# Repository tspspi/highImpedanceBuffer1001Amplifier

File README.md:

# Simple combined buffer and 1001x amplifier

This is a simple circuit that combines two OpAmps with 1 GHz
bandwidth to form a buffer amplifier followed by an 1001 times
amplifying amplifier.

This circuit has been designed to measure the beam profile of
an low current electron beam. The shunt has been designed as wire
resistor to be easily adaptable. The OpAmps have been selected
with up to 1 GHz bandwidth to allow for measurement of deflection
frequency inside an modulated beam.

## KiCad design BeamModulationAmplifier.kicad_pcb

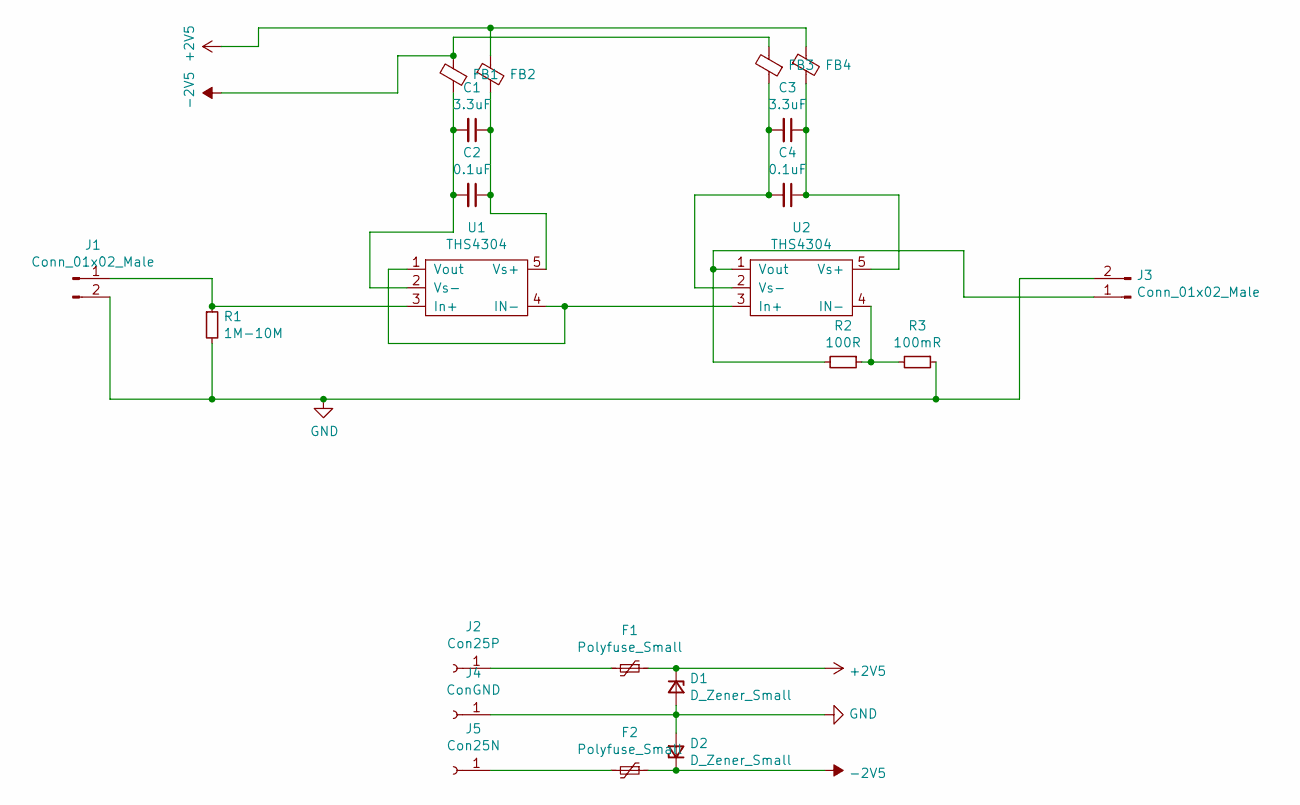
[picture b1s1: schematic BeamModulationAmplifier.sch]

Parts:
C1, C3: 3.3uF; R_0805_2012Metric
C2, C4: 0.1uF; R_0805_2012Metric
D1, D2: D_Zener_Small; Mini2
F1, F2: Polyfuse_Small; Generic2016
FB1, FB2, FB3, FB4: Ferrite_Bead_Small; R_0603_1608Metric; FarnellNo 3282195
J1, J3: Conn_01x02_Male; BNC_Amphenol_B6252HB-NPP3G-50_Horizontal; FarnellNo 1076296
J2: Con25P; 24.243
J4: ConGND; 24.243
J5: Con25N; 24.243
R1: 1M-10M; R_Axial_DIN0309_L9.0mm_D3.2mm_P15.24mm_Horizontal
R2: 100R; R_0805_2012Metric
R3: 100mR; R_0805_2012Metric
U1, U2: THS4304; SOT-23-5

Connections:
+2V5: D1.1 (K), F1.1, FB2.1, FB4.1
-2V5: D2.1 (K), F2.1, FB1.2, FB3.2
GND: D1.2 (A), D2.2 (A), J1.2, J3.2, J4.1, R1.2, R3.1
unnamed: C1.1, C2.1, FB2.2, U1.5 (Vs+)
unnamed: C1.2, C2.2, FB1.1, U1.2 (Vs-)
unnamed: C3.1, C4.1, FB4.2, U2.5 (Vs+)
unnamed: C3.2, C4.2, FB3.1, U2.2 (Vs-)
unnamed: F1.2, J2.1, J2.2
unnamed: F2.2, J5.1, J5.2
unnamed: J1.1, R1.1, U1.3 (In+)
unnamed: J3.1, R2.2, U2.1 (Vout)
unnamed: R2.1, R3.2, U2.4 (IN-)
unnamed: U1.1 (Vout), U1.4 (IN-), U2.3 (In+)

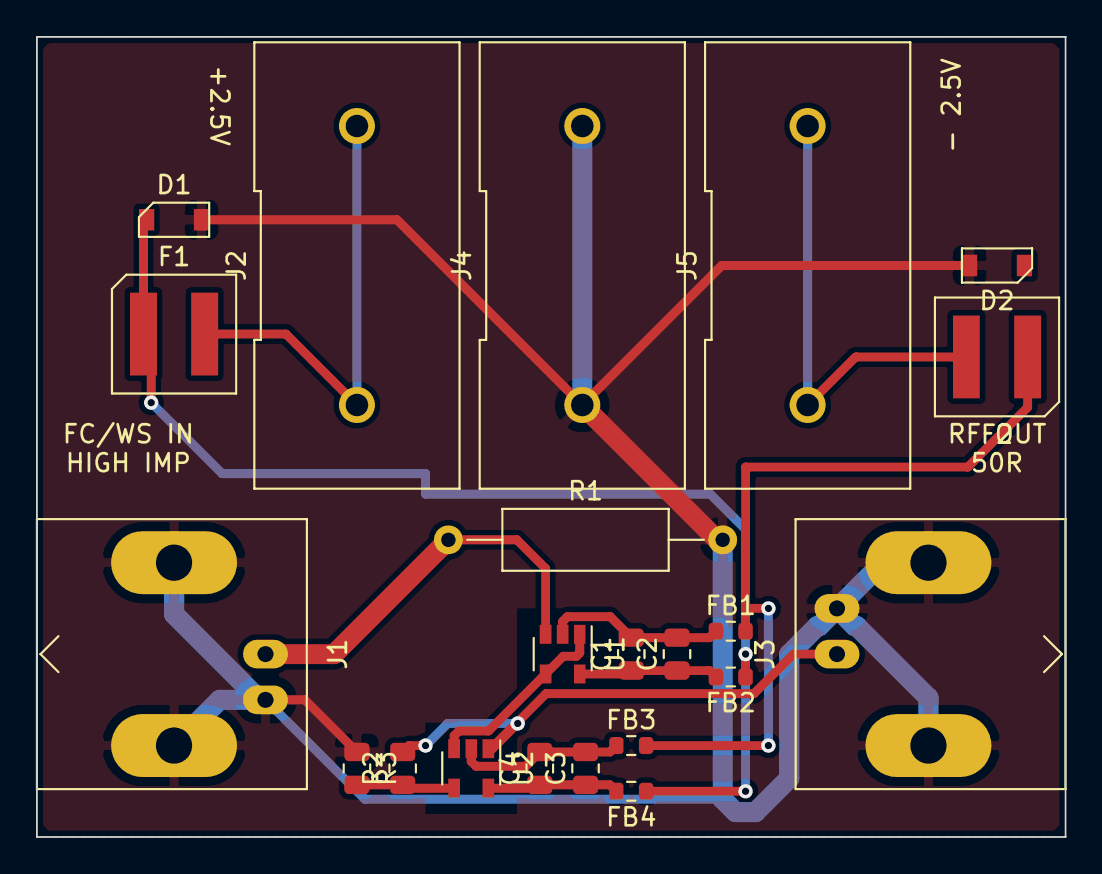
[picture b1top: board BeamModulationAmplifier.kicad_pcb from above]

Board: 2 copper layers, 57.2 x 44.5 mm, 22 parts (0 on the bottom side), 13 nets.

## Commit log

2020-10-29 Initial commit including Farnell BOM
2020-10-29 Added license
2020-10-29 Added images
2020-10-29 Adding images to README
2020-10-31 Modified README.md
